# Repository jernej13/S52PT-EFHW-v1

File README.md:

# S52PT-EFHW-v1
End Fed Half Wave antenna. Multiband 7MHz, 14MHz and 21MHz.

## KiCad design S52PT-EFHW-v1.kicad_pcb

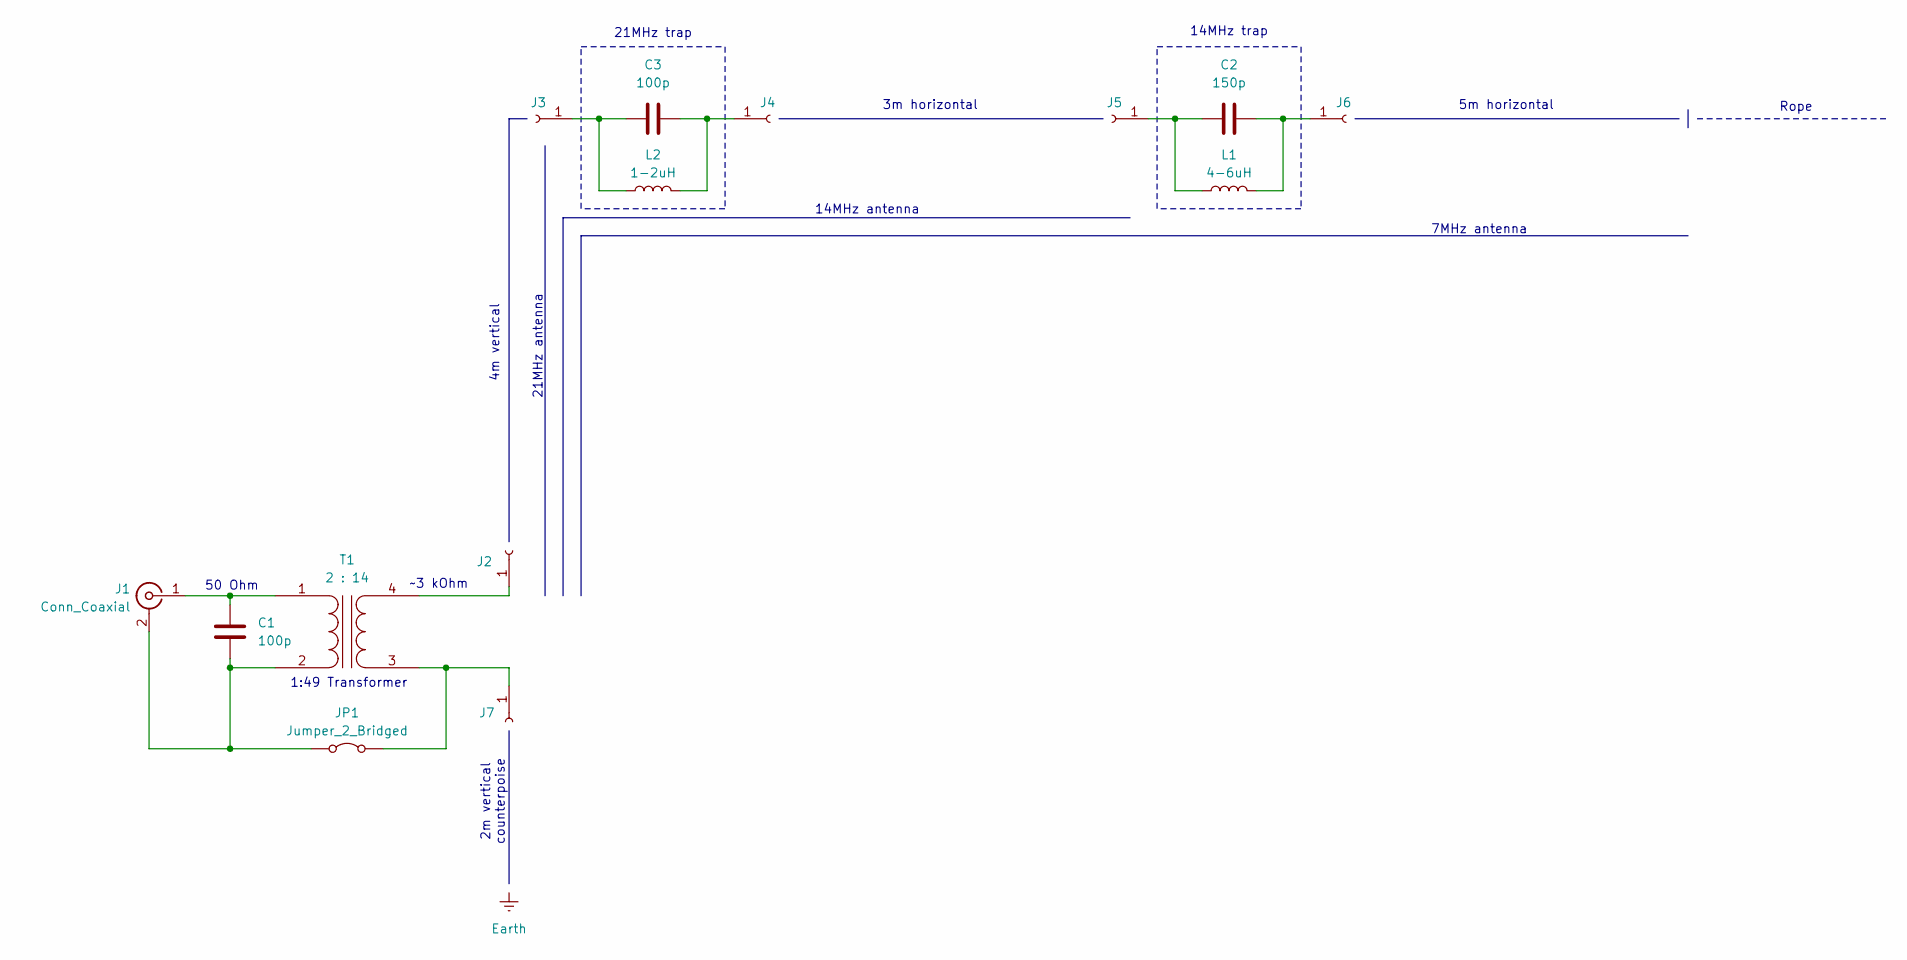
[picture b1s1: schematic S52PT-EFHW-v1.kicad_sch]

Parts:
C1, C3: 100p; C_Disc_D6.0mm_W4.4mm_P5.00mm
C2: 150p; C_Disc_D6.0mm_W4.4mm_P5.00mm
J1: Conn_Coaxial; Coax
J2, J3, J4, J5, J6, J7: Conn_01x01_Socket; Connector
JP1: Jumper_2_Bridged; Jumper_Harwin_S1621_P10.9mm
L1: 4-6uH; Inductor_21M
L2: 1-2uH; Inductor_14M
T1: 2 : 14; Transformer_Toroid_Horizontal_D14.0mm_Amidon-T50

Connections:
unnamed: C1.1, J1.2 (Ext), JP1.1 (A), T1.2 (AB)
unnamed: C1.2, J1.1 (In), T1.1 (AA)
unnamed: J2.1 (Pin_1_1), T1.4 (SB)
unnamed: C3.2, J3.1 (Pin_1_1), L2.1
unnamed: C3.1, J4.1 (Pin_1_1), L2.2
unnamed: C2.2, J5.1 (Pin_1_1), L1.1
unnamed: C2.1, J6.1 (Pin_1_1), L1.2
unnamed: J7.1 (Pin_1_1), JP1.2 (B), T1.3 (SA)

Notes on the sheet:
1:49 Transformer
21MHz antenna
4m vertical
2m vertical counterpoise
21MHz trap
3m horizontal
~3 kOhm
14MHz antenna
Rope
5m horizontal
7MHz antenna
50 Ohm
14MHz trap

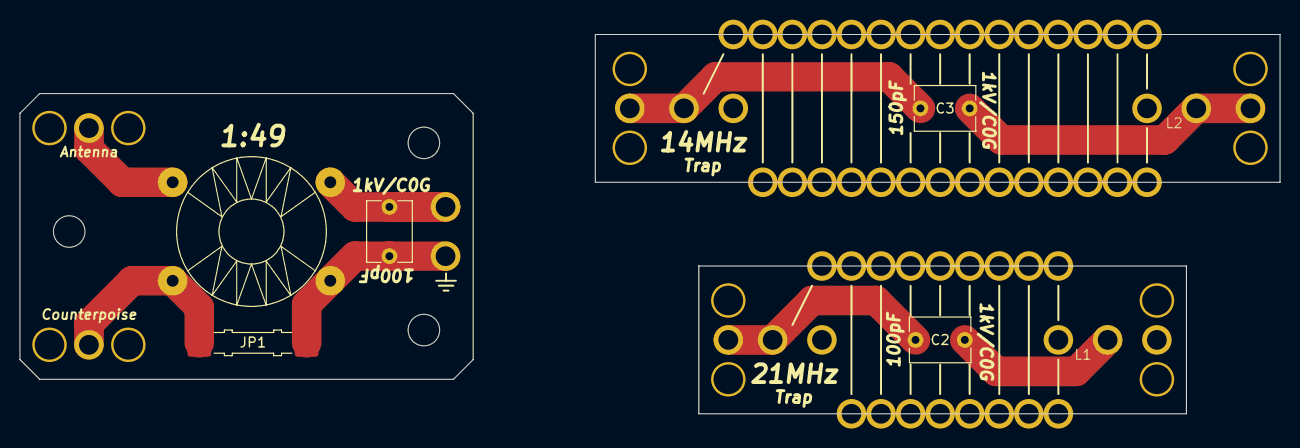
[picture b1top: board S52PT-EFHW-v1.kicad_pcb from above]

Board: 2 copper layers, 127.9 x 38.5 mm, 14 parts (0 on the bottom side), 8 nets.

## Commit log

2026-05-09 Drawn schematics and PCB for first iteration.
